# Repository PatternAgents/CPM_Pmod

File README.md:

CPM Pmod Adaptor
====================

PatternAgents CPM Pmod Adaptor

[  
*PatternAgents CPM Pmod Adaptor*](http://www.patternagents.com/projects/CPM_Pmod.html)

The "CPM Pmod Adaptor" board is designed to enable Cypress PSoC development boards to utilize Pmod peripherals.

The PatternAgents "CPM Pmod Adaptor" board supports :

Cypress CY8CKIT-001 : (Supports up to three (3) "CPM Pmod Adaptor")

Cypress CY8CKIT-030 : (Supports up to two (2) "CPM Pmod Adaptor")

Cypress CY8CKIT-050 : (Supports up to two (2) "CPM Pmod Adaptor")

Cypress CY3280-28xxx : (Supports one (1) "CPM Pmod Adaptor")

Cypress CY3280-22x45 : (Supports one (1) "CPM Pmod Adaptor")

(Not an Exhaustive list as more Cypress development boards are routinely released)

For information on the Digilent Pmod Specification, see http://www.digilentinc.com/Pmods/Digilent-Pmod_%20Interface_Specification.pdf

[  
*Licensing CC BY-NC-SA 4.0*](http://creativecommons.org/licenses/by-nc-sa/4.0/)

PatternAgents uses the increasingly popular business model called "Dual Licensing" 
in which both the open source software distribution mechanism and traditional commercial software distribution models are combined.

Open Source Projects:        

If you are developing and distributing open source applications under the Creative Commons CC BY-NC-SA 4.0, 
as published by the Creative Commons Foundation, then you are free to use the PatternAgents hardware/software under the CC BY-NC-SA 4.0 license. 
Please note that CC BY-NC-SA 4.0 requires that all modifications to the original code as well as all Derivative Works 
must also be released under the terms of the CC BY-NC-SA 4.0 license.

Closed Source Projects:

If you are developing and distributing traditional closed source or commercial applications, 
you must purchase a PatternAgents commercial use license, 
which is specifically designed for users interested in retaining the proprietary status of their designs and code. 
All PatternAgents commercial licenses expressly supersede the CC BY-NC-SA 4.0 license. 
This means that when you license the PatternAgents software under a commercial license, 
you specifically do not use the software under the CC BY-NC-SA 4.0 license and therefore you are not subject to any of its terms.
        
If you would like to use our designs for your own personal or educational use, have at it! 

Our public design repository is available at <a href="https://github.com/patternagents">Github</a>.

If you would like to produce our designs for commercial use, or as products for sale, 
please contact us to arrange for a Commercial Use license. We have many other designs, 
as well as options and extras that are not released publicly. 
We will also customize designs, firmware, and software for a reasonable fee, just contact us to discuss your requirements.

THIS SOFTWARE IS PROVIDED BY THE CONTRIBUTORS "AS IS" AND WITHOUT ANY EXPRESS OR IMPLIED WARRANTIES, 
INCLUDING, BUT NOT LIMITED TO, THE IMPLIED WARRANTIES OF MERCHANTABILITY AND FITNESS FOR A PARTICULAR PURPOSE ARE DISCLAIMED. 
IN NO EVENT SHALL THE COPYRIGHT OWNER OR CONTRIBUTORS BE LIABLE FOR ANY DIRECT, INDIRECT, INCIDENTAL, SPECIAL, EXEMPLARY, 
OR CONSEQUENTIAL DAMAGES (INCLUDING, BUT NOT LIMITED TO, PROCUREMENT OF SUBSTITUTE GOODS OR SERVICES; LOSS OF USE, DATA, 
OR PROFITS; OR BUSINESS INTERRUPTION) HOWEVER CAUSED AND ON ANY THEORY OF LIABILITY, WHETHER IN CONTRACT, 
STRICT LIABILITY, OR TORT (INCLUDING NEGLIGENCE OR OTHERWISE) ARISING IN ANY WAY OUT OF THE USE OF THIS SOFTWARE, 
EVEN IF ADVISED OF THE POSSIBILITY OF SUCH DAMAGE. 

-------------------------------------------------------------------------------------------

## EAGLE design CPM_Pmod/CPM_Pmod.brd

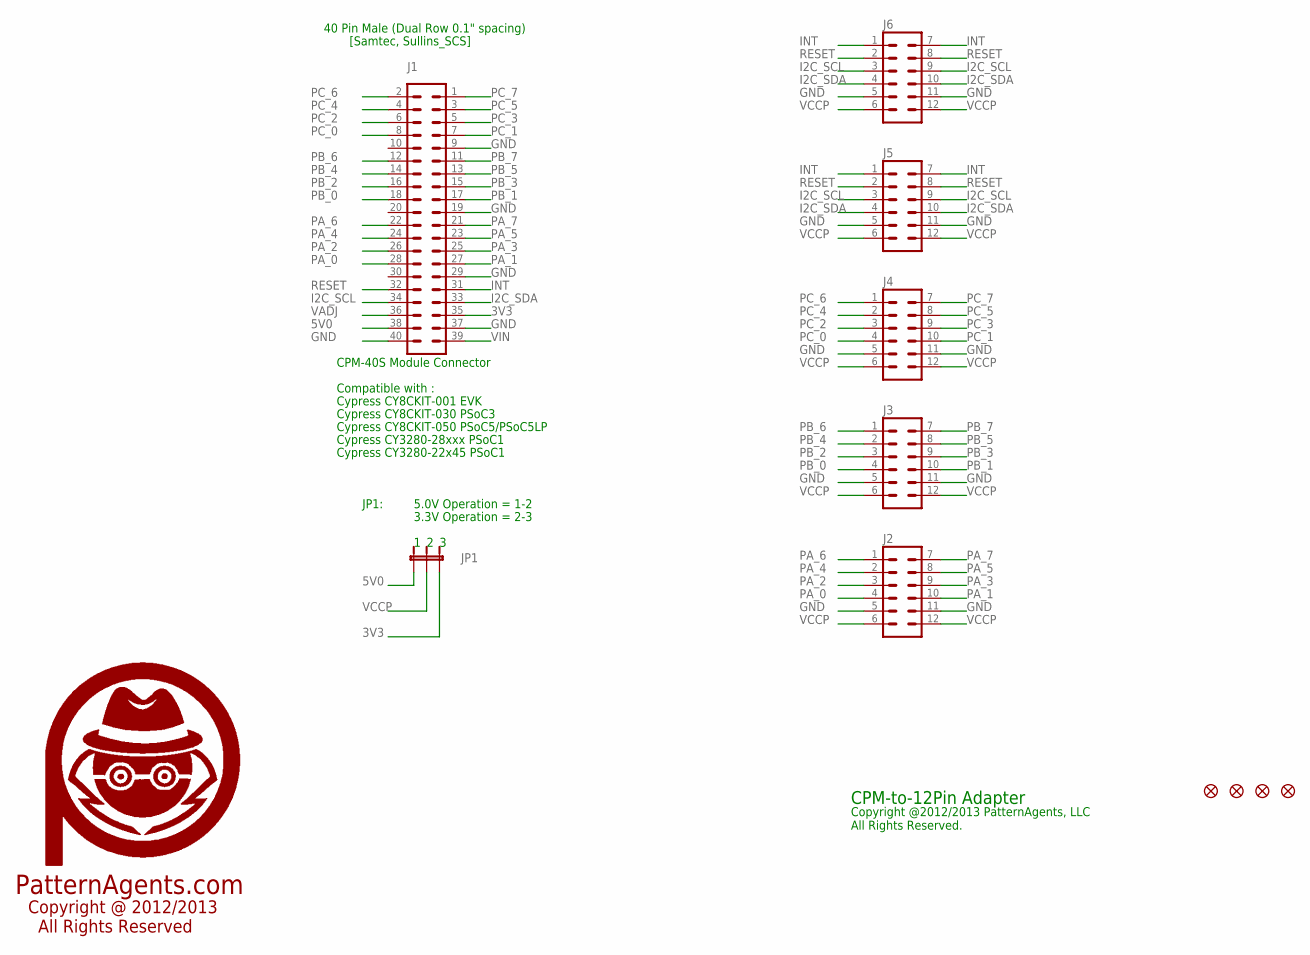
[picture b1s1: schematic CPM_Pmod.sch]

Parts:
J1: SULLINS_SCS; MA20-2
J2, J3, J4, J5, J6: MA06-2-PMOD
JP1: JUMPER-3PTH; 1X03
JP2, JP3, JP4, JP5: FIDUCIAL1.5X3; FIDUCIAL-1.5X3
U$1: LOGO_PA_AGENTLARGE; LOGO_PA_AGENT_LARGE

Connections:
3V3: J1.35, JP1.3
5V0: J1.38, JP1.1
GND: J1.9, J1.19, J1.29, J1.37, J1.40, J2.5, J2.11, J3.5, J3.11, J4.5, J4.11, J5.5, J5.11, J6.5, J6.11
I2C_SCL: J1.34, J5.3, J5.9, J6.3, J6.9
I2C_SDA: J1.33, J5.4, J5.10, J6.4, J6.10
INT: J1.31, J5.1, J5.7, J6.1, J6.7
PA_0: J1.28, J2.4
PA_1: J1.27, J2.10
PA_2: J1.26, J2.3
PA_3: J1.25, J2.9
PA_4: J1.24, J2.2
PA_5: J1.23, J2.8
PA_6: J1.22, J2.1
PA_7: J1.21, J2.7
PB_0: J1.18, J3.4
PB_1: J1.17, J3.10
PB_2: J1.16, J3.3
PB_3: J1.15, J3.9
PB_4: J1.14, J3.2
PB_5: J1.13, J3.8
PB_6: J1.12, J3.1
PB_7: J1.11, J3.7
PC_0: J1.8, J4.4
PC_1: J1.7, J4.10
PC_2: J1.6, J4.3
PC_3: J1.5, J4.9
PC_4: J1.4, J4.2
PC_5: J1.3, J4.8
PC_6: J1.2, J4.1
PC_7: J1.1, J4.7
RESET: J1.32, J5.2, J5.8, J6.2, J6.8
VADJ: J1.36
VCCP: J2.6, J2.12, J3.6, J3.12, J4.6, J4.12, J5.6, J5.12, J6.6, J6.12, JP1.2
VIN: J1.39

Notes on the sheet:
[Samtec, Sullins_SCS]
40 Pin Male (Dual Row 0.1" spacing)
CPM-40S Module Connector
Compatible with :
Cypress CY8CKIT-001 EVK
Cypress CY8CKIT-030 PSoC3
Cypress CY3280-28xxx PSoC1
Cypress CY3280-22x45 PSoC1
Cypress CY8CKIT-050 PSoC5/PSoC5LP
JP1:
5.0V Operation = 1-2
3.3V Operation = 2-3
CPM-to-12Pin Adapter
Copyright @2012/2013 PatternAgents, LLC All Rights Reserved.
PatternAgents.com
Copyright @ 2012/2013 All Rights Reserved

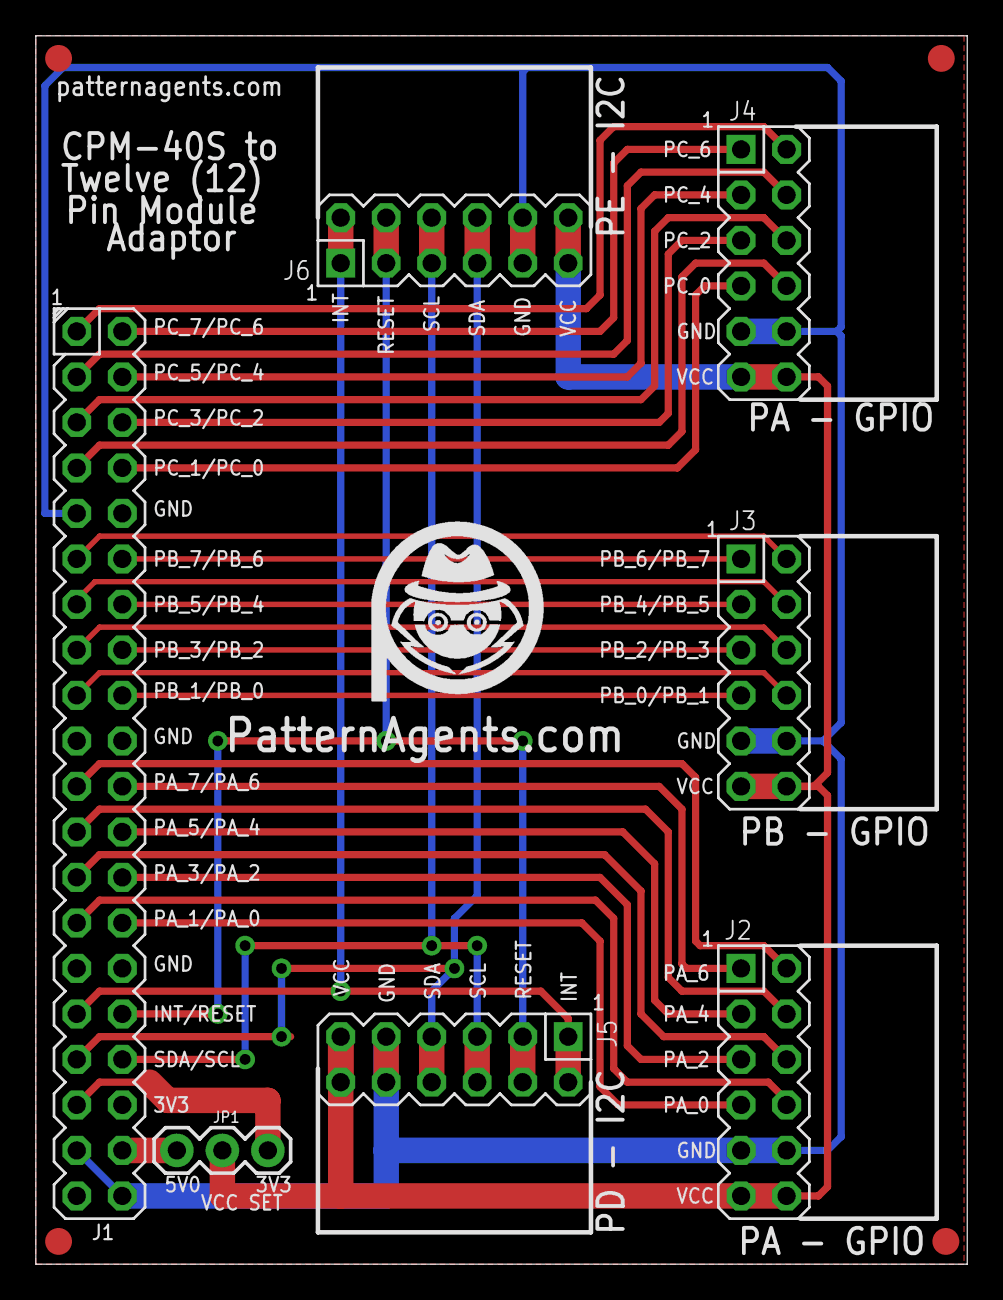
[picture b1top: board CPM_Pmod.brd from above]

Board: 2 copper layers, 52.0 x 68.6 mm, 13 parts (1 on the bottom side), 32 nets.

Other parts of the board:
U$3: LOGO_PA_AGENTLARGE; LOGO_PA_AGENT_LARGE

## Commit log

2013-07-17 initial create project
2013-07-18 Add GPLv3/Dual license files
2013-07-18 Fix Image Link
2013-07-18 Add Eagle design files
2013-07-18 remove backup file
2013-07-19 link fixes
2013-07-22 reduce png file sizes
2013-11-17 Eagle project file update
2013-12-23 Move Licensing to CC 4.0

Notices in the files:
parts and their libraries:
SparkFun: Licensing: CC v3.0 Share-Alike You are welcome to use this library for commercial purposes.
